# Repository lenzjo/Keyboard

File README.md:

Hardware keyboard decoder

This is my attempt at making a versatile keyboard decoder. The project is documented at http://tlcstuff.uk/6502/a-keyboard-and-other-good-stuff/

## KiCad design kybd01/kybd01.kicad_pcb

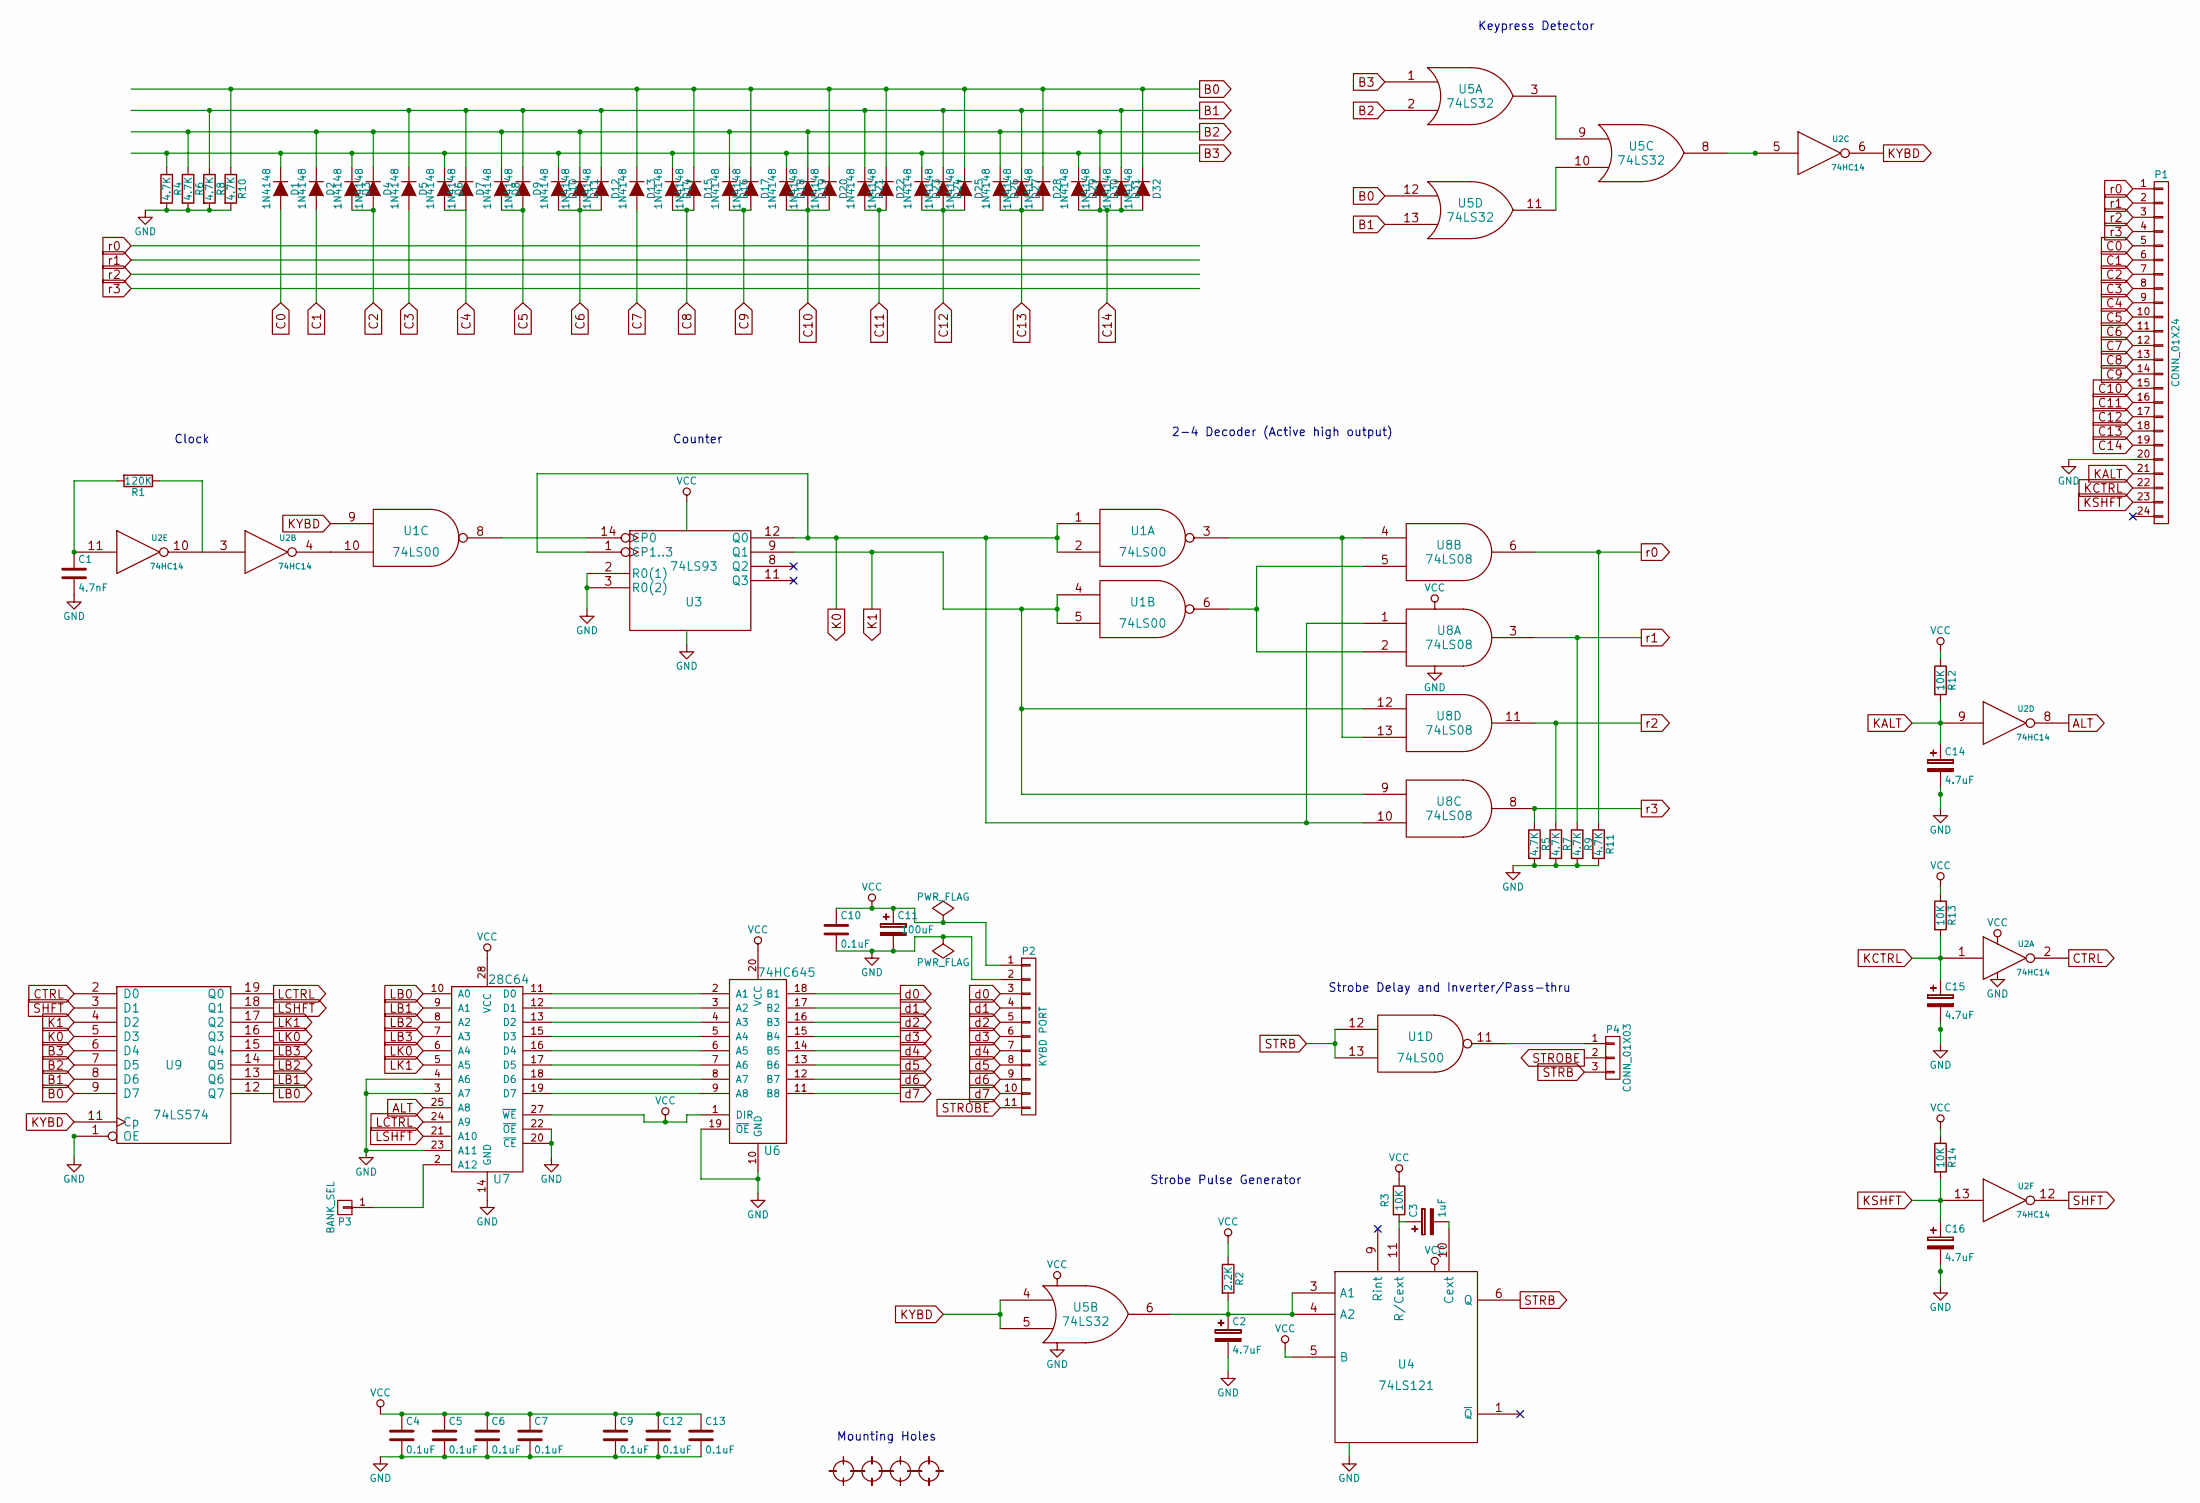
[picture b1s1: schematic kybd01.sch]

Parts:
C1: 4.7nF; C_Rect_L7_W2.5_P5
C2: 4.7uF; Elko_vert_11.2x6.3mm_RM2.5
C3: 1uF; Elko_vert_11.2x6.3mm_RM2.5
C4, C5, C6, C7, C9, C10, C12, C13: 0.1uF; C_Rect_L4_W2.5_P2.5
C11: 100uF; Elko_vert_11x5mm_RM2.5
C14, C15, C16: 4.7uF; Elko_vert_11x5mm_RM2.5
D1, D2, D3, D4, D5, D6, D7, D8, D9, D10, D11, D12, D13, D14, D15, D16, D17, D18, D19, D20, D21, D22, D23, D24, D25, D26, D27, D28, D29, D30, D31, D32: 1N4148; Resistor_Horizontal_RM10mm
MH1, MH2, MH3, MH4: myhole; Mounting_Hole
P1: CONN_01X24; Pin_Header_Straight_1x24
P2: KYBD PORT; Pin_Header_Straight_1x11
P3: BANK_SEL; Pin_Header_Straight_1x01
P4: CONN_01X03; Pin_Header_Straight_1x03
R1: 120K; Resistor_Horizontal_RM10mm
R2: 2.2K; Resistor_Horizontal_RM10mm
R3, R12, R13, R14: 10K; Resistor_Horizontal_RM10mm
R4, R5, R6, R7, R8, R9, R10, R11: 4.7K; Resistor_Horizontal_RM10mm
U1: 74LS00; DIP14-0.3
U2: 74HC14; DIP14-0.3
U3: 74LS93; DIP14-0.3
U4: 74LS121; DIP14-0.3
U5: 74LS32; DIP14-0.3
U6: 74HC645; DIP20-0.3
U7: 28C64; DIP28-0.6
U8: 74LS08; DIP14-0.3
U9: 74LS574; DIP20-0.3

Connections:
ALT: U2.8, U7.25 (A8)
B0: D13.1 (K), D15.1 (K), D17.1 (K), D20.1 (K), D22.1 (K), D25.1 (K), D28.1 (K), D32.1 (K), R10.1, U5.12, U9.9 (D7)
B1: D5.1 (K), D7.1 (K), D9.1 (K), D12.1 (K), D21.1 (K), D24.1 (K), D27.1 (K), D31.1 (K), R8.1, U5.13, U9.8 (D6)
B2: D2.1 (K), D4.1 (K), D8.1 (K), D11.1 (K), D16.1 (K), D19.1 (K), D26.1 (K), D30.1 (K), R6.1, U5.2, U9.7 (D5)
B3: D1.1 (K), D3.1 (K), D6.1 (K), D10.1 (K), D14.1 (K), D18.1 (K), D23.1 (K), D29.1 (K), R4.1, U5.1, U9.6 (D4)
C0: D1.2 (A), P1.5
C1: D2.2 (A), P1.6
C2: D3.2 (A), D4.2 (A), P1.7
C3: D5.2 (A), P1.8
C4: D6.2 (A), D7.2 (A), P1.9
C5: D8.2 (A), D9.2 (A), P1.10
C6: D10.2 (A), D11.2 (A), D12.2 (A), P1.11
C7: D13.2 (A), P1.12
C8: D14.2 (A), D15.2 (A), P1.13
C9: D16.2 (A), D17.2 (A), P1.14
C10: D18.2 (A), D19.2 (A), D20.2 (A), P1.15
C11: D21.2 (A), D22.2 (A), P1.16
C12: D23.2 (A), D24.2 (A), D25.2 (A), P1.17
C13: D26.2 (A), D27.2 (A), D28.2 (A), P1.18
C14: D29.2 (A), D30.2 (A), D31.2 (A), D32.2 (A), P1.19
CTRL: U2.2, U9.2 (D0)
GND: C1.2, C2.2, C4.2, C5.2, C6.2, C7.2, C9.2, C10.2, C11.2, C12.2, C13.2, C14.2, C15.2, C16.2, P1.20, P2.2, R4.2, R5.2, R6.2, R7.2, R8.2, R9.2, R10.2, R11.2, U1.7 (GND), U2.7 (GND), U3.2 (R0(1)), U3.3 (R0(2)), U3.10 (GND), U4.7 (GND), U5.7 (GND), U6.10 (GND), U6.19 (~OE), U7.3 (A7), U7.4 (A6), U7.14 (GND), U7.20 (~CE), U7.22 (~OE), U7.23 (A11), U7.26 (NC), U8.7 (GND), U9.1 (OE), U9.10 (GND)
K0: U1.1, U1.2, U3.1 (CP1..3), U3.12 (Q0), U8.1, U8.10, U9.5 (D3)
K1: U1.4, U1.5, U3.9 (Q1), U8.9, U8.12, U9.4 (D2)
KALT: C14.1, P1.21, R12.2, U2.9
KCTRL: C15.1, P1.22, R13.2, U2.1
KSHFT: C16.1, P1.23, R14.2, U2.13
KYBD: U1.9, U2.6, U5.4, U5.5, U9.11 (Cp)
LB0: U7.10 (A0), U9.12 (Q7)
LB1: U7.9 (A1), U9.13 (Q6)
LB2: U7.8 (A2), U9.14 (Q5)
LB3: U7.7 (A3), U9.15 (Q4)
LCTRL: U7.24 (A9), U9.19 (Q0)
LK0: U7.6 (A4), U9.16 (Q3)
LK1: U7.5 (A5), U9.17 (Q2)
LSHFT: U7.21 (A10), U9.18 (Q1)
unnamed: C1.1, R1.2, U2.11
unnamed: C2.1, R2.2, U4.3 (A1), U4.4 (A2), U5.6
unnamed: C3.1, R3.2, U4.11 (R/Cext)
unnamed: C3.2, U4.10 (Cext)
unnamed: P3.1, U7.2 (A12)
unnamed: P4.1, U1.11
unnamed: R1.1, U2.3, U2.10
unnamed: U1.3, U8.4, U8.13
unnamed: U1.6, U8.2, U8.5
unnamed: U1.8, U3.14 (CP0)
unnamed: U1.10, U2.4
unnamed: U2.5, U5.8
unnamed: U5.3, U5.9
unnamed: U5.10, U5.11
unnamed: U6.2 (A1), U7.11 (D0)
unnamed: U6.3 (A2), U7.12 (D1)
unnamed: U6.4 (A3), U7.13 (D2)
unnamed: U6.5 (A4), U7.15 (D3)
unnamed: U6.6 (A5), U7.16 (D4)
unnamed: U6.7 (A6), U7.17 (D5)
unnamed: U6.8 (A7), U7.18 (D6)
unnamed: U6.9 (A8), U7.19 (D7)
SHFT: U2.12, U9.3 (D1)
STRB: P4.3, U1.12, U1.13, U4.6 (Q)
STROBE: P2.11, P4.2
VCC: C4.1, C5.1, C6.1, C7.1, C9.1, C10.1, C11.1, C12.1, C13.1, P2.1, R2.1, R3.1, R12.1, R13.1, R14.1, U1.14 (VCC), U2.14 (VCC), U3.5 (VCC), U4.5 (B), U4.14 (VCC), U5.14 (VCC), U6.1 (DIR), U6.20 (VCC), U7.27 (~WE), U7.28 (VCC), U8.14 (VCC), U9.20 (VCC)
d0: P2.3, U6.18 (B1)
d1: P2.4, U6.17 (B2)
d2: P2.5, U6.16 (B3)
d3: P2.6, U6.15 (B4)
d4: P2.7, U6.14 (B5)
d5: P2.8, U6.13 (B6)
d6: P2.9, U6.12 (B7)
d7: P2.10, U6.11 (B8)
r0: P1.1, R11.1, U8.6
r1: P1.2, R9.1, U8.3
r2: P1.3, R7.1, U8.11
r3: P1.4, R5.1, U8.8

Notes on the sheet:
Mounting Holes
Clock
Counter
2-4 Decoder (Active high output)
Strobe Pulse Generator
Keypress Detector
Strobe Delay and Inverter/Pass-thru

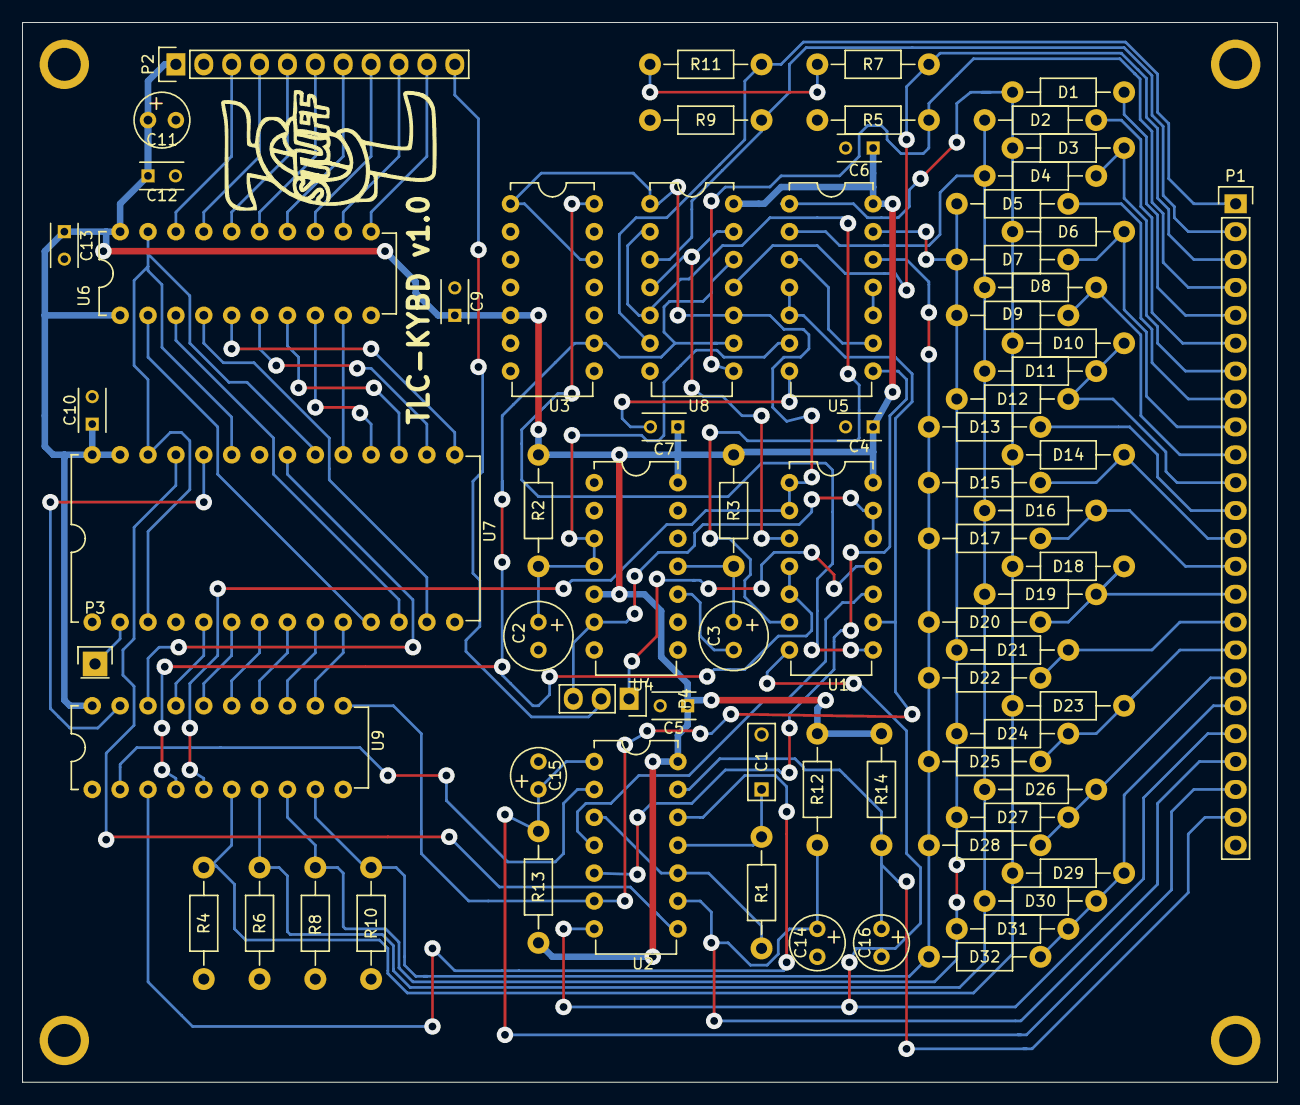
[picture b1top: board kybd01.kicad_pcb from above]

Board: 2 copper layers, 114.3 x 96.5 mm, 78 parts (0 on the bottom side), 74 nets.

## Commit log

2015-12-12 initial upload
